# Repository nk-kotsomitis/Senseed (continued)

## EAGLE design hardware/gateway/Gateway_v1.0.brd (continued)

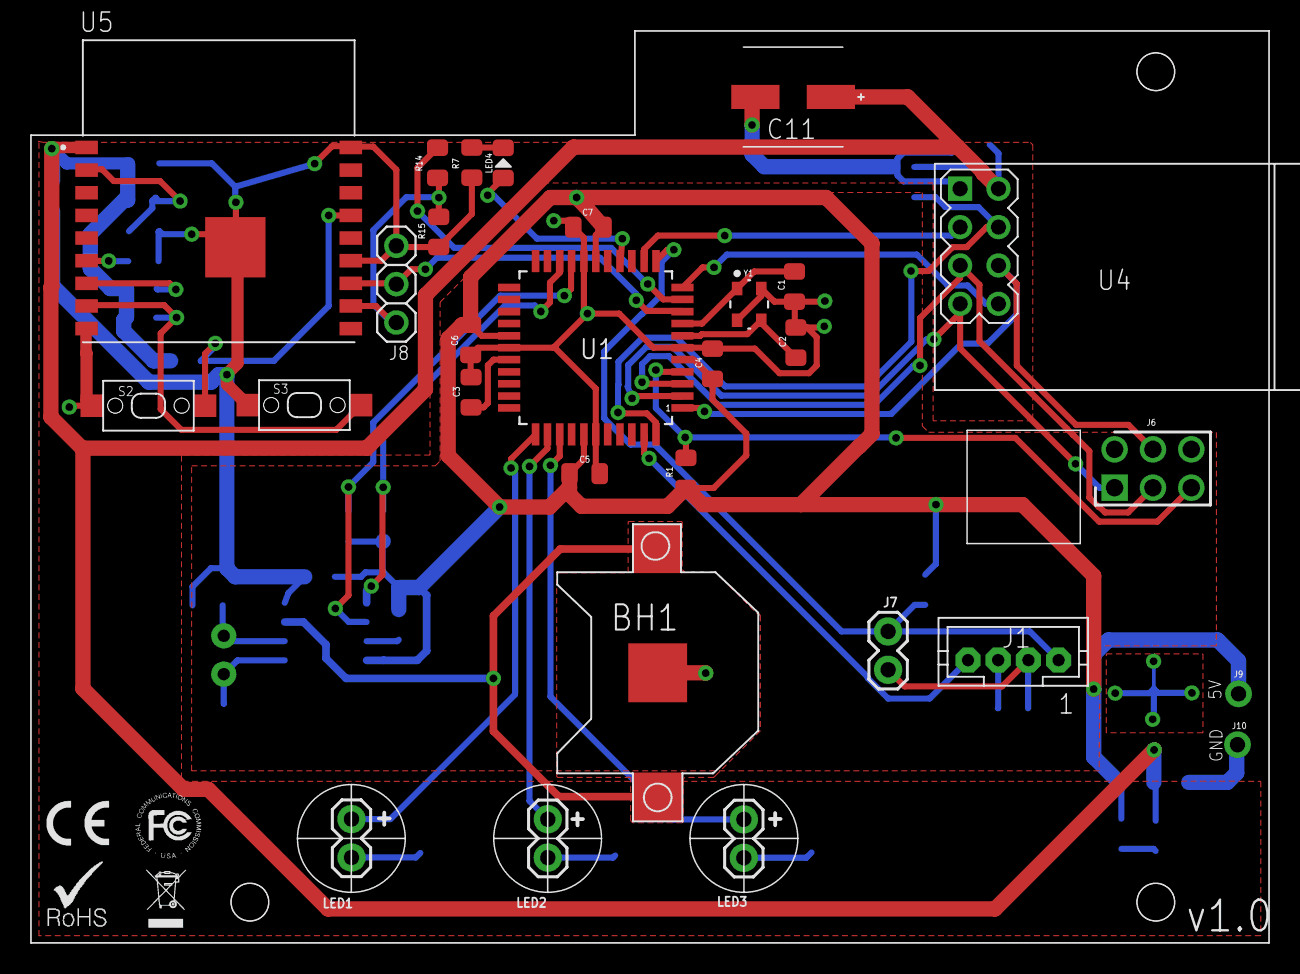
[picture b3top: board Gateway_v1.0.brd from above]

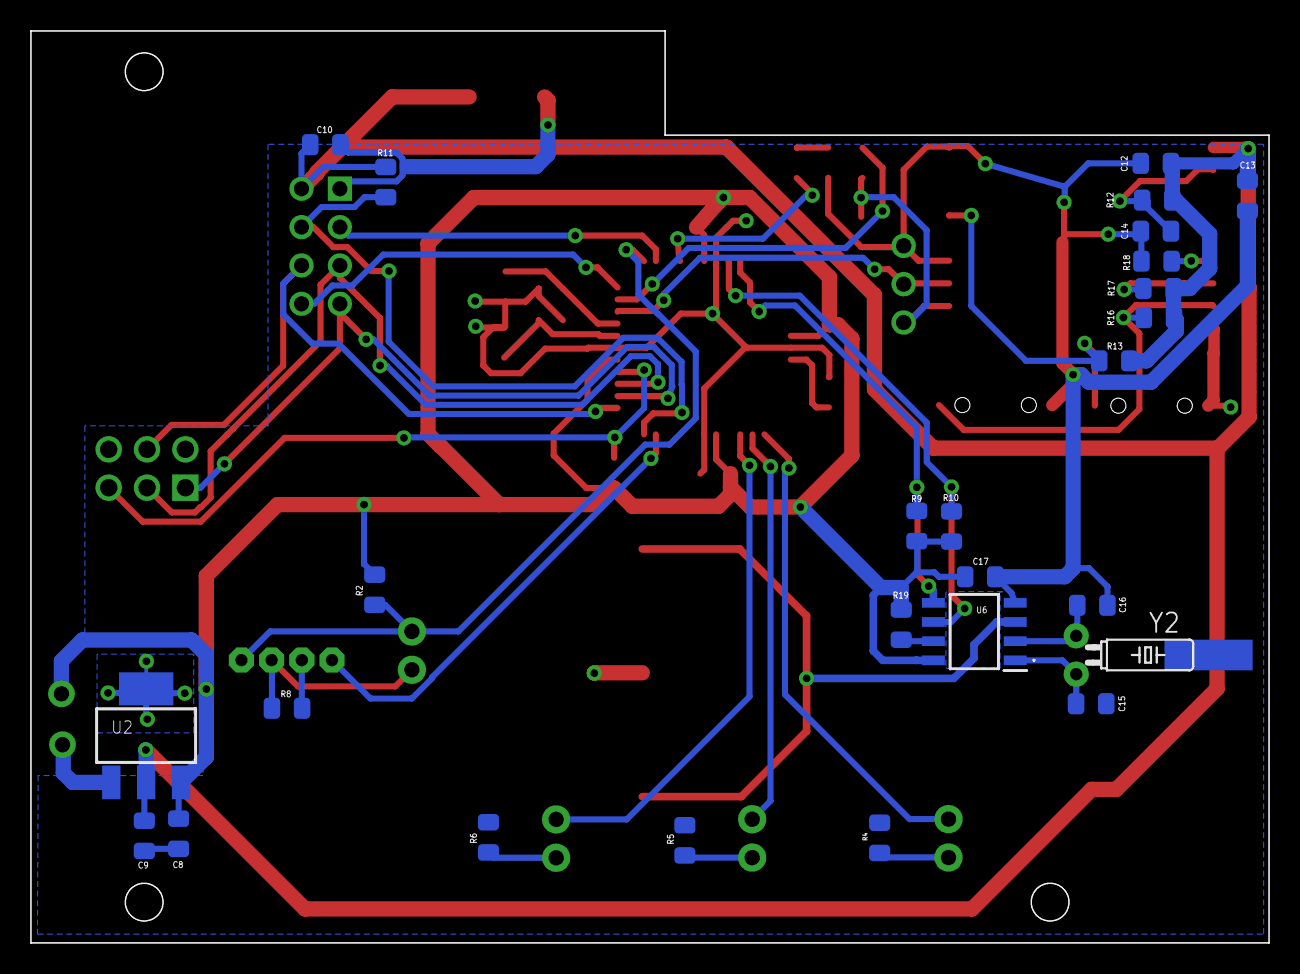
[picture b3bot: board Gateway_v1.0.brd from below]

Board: 2 copper layers, 82.0 x 60.4 mm, 55 parts (26 on the bottom side), 38 nets.

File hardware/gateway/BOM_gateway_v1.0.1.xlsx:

# | Reference Designators | Quantity | MPN | Manufacturer | Part Description | Value | Package | Remark or Link
1 | U1 | 1 | ATMEGA1284-AU | Microchip Technology / Atmel | 8-bit Microcontrollers - MCU AVR 128KB FLSH 4KB EE16KB SRAM-20 MHz | - | TQFP-44
2 | U2 | 1 | SPX1117M3-L-3-3/TR | Maxlinear | LDO Voltage Regulators 3.3V 0.8A Positive | 3.3V 0.8A | SOT-223-3
3 | U4 | 1 | - | - | NRF24L01+ 2.4GHz Wireless RF Transceiver Module | - | Plug In Module - 2x4 2.54mm header | Customer Provided
4 | U5 | 1 | ESP-WROOM-02D(M1102H1600PH3Q0) | Espressif Systems | WiFi Modules (802.11) SMD Module, ESP8266EX, 16Mbits SPI flash, UART Mode, PCB 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 | - | SMD module
5 | U6 | 1 | MCP79410T-I/SN | Microchip Technology | Real Time Clock I2C GP RTCC 1Kb EE 64B SRAM ID | - | SOIC-8
6 | BH1 | 1 | MY-1220-03 | MYOUNG | Coin Cell Battery Holder CR1220 SMT | - | SMD
7 | Y1 | 1 | TXM16M0004322KBCDO00T | TAE(Zhejiang Abel Elec) | ±10ppm 16000000Hz -40℃~85℃ 18pF SMD Passive Crystal Oscillator 35Ω SMD3225-4P C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 | 16 MHz | SMD3225-4P
8 | Y2 | 1 | JFWSH32K25A104C | SHENZHEN JINGFA ELECTRONICS | Radial Cylinder Crystal 32.768KHz ±20ppm 12.5pF 30 KOhm(Max) Radial,3x8mm | 32.768 kHz | OSC-TH Radial 3x8mm
9 | J1 | 1 | PH2.0-4P | CAX | 4-Pin Low-profile PH2.0 Housing Connector | 4 Position | Through Hole
10 | LED1, LED2, LED3 | 3 | 204-10SUGC/S400-A5-L | Everlight Elec | Green 525nm Through Hole 3mm Light Emitting Diodes (LED) - Water Clear | 3mm Green - Clear | Through Hole
11 | LED1, LED2, LED3 | 3 | ERM 1-955 | Bivar | LED Mounting Hardware LED Mount Self Ret Universal LED Black | T-1 3/4 (5mm) | - | Led Spacer
12 | J6 | 1 | C65114 | BOOMELE(Boom Precision Elec) | 2 2.54mm 6 Straight Header，Breakaway P=2.54mm Pin Headers | 6 Position | Through Hole
13 | J7 | 1 | PZ254V-11-02P | XFCN | 2.54mm Straight 2 1 Header，Breakaway Through Hole,P=2.54mm Pin Headers | 2 Position | Through Hole
14 | J8 | 1 | C49257 | BOOMELE(Boom Precision Elec) | 3 2.54mm Straight 1 Header，Breakaway Through Hole Pin Headers | 3 Position | Through Hole
15 | S2, S3 | 2 | TS-1096S-A2B2-C1D2 | Yuandi | SPST Vertical Tactile Switch 3X6X5.0mm SMT | - | SMD
16 | C15, C16 | 2 | 0805CG150J500NT |  | Multilayer Ceramic Capacitor MLCC 15pF ±5% 0805 SMD | 15pF | 0805
17 | C1, C2 | 2 | 0805CG270J500NT |  | Multilayer Ceramic Capacitor MLCC 27pF ±5% 0805 SMD | 27pF | 0805
18 | C3, C4, C5, C6, C7, C13, C14, C17 | 8 | 0805B104M500NT |  | Multilayer Ceramic Capacitor MLCC 100nF ±5% 0805 SMD | 100nF | 0805
19 | C9 | 1 | CL21B225KOFNNNE |  | Multilayer Ceramic Capacitor MLCC 2.2uF X7R ±10% 16V 0805 SMD | 2.2uF | 0805
20 | C8 | 1 | CL21A475KAQNNNE |  | Multilayer Ceramic Capacitor MLCC 4.7uF X5R ±10% 25V 0805 SMD | 4.7uF | 0805
21 | C10, C12 | 2 | GRM21BR61C106KE15L |  | X5R ±10% 16V 10uF 0805 Multilayer Ceramic Capacitors MLCC - SMD/SMT | 10uF | 0805
22 | C11 | 1 | VD1A331ME077000CE0 | Changzhou Huawei Electronics | 6.3mm 330uF 7.7mm 10V 2000hrs 105℃ ±20% -45℃~+105℃ SMD,6.3x7.7mm Aluminum Elect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 | 330uF | 6.3x7.7 SMD
23 | R1, R2, R11, R12, R13, R16, R17, R18 | 8 | 0805W8J1002T5E |  | Chip Resistor - Surface Mount 10K ±5% 1/8W 0805 | 10K | 0805
24 | R14 | 1 | 0805W8J1001T5E |  | Chip Resistor - Surface Mount 1K ±5% 1/8W 0805 | 1K | 0805
25 | R15 | 1 | 0805W8J2001T5E |  | Chip Resistor - Surface Mount 2K ±5% 1/8W 0805 | 2K | 0805
26 | R4, R5, R6, R7, R8, R9, R10, R19 | 8 | 0805W8J0472T5E |  | Chip Resistor - Surface Mount 4.7K ±5% 1/8W 0805 | 4K7 | 0805
 | Off-board components
27 | - | 1 | TC013-N11ASKKUGXX | Well Buying | Tactile Switches TACTILE/JOG SWITCH SPST50mA 12VDC180gf | Illuminated | -
28 | - | 3 | CMC_313_GTP | Visual Communications Company (VCC) | LED Lenses Green Diffused 5mm CMC313GTP | Green | -
29 | - | 1 | - | - | PH2.0 PH 2.0 4pin PH-4p connector with cable 100mm wire 24AWG | PH-4p 100mm 24AWG | -

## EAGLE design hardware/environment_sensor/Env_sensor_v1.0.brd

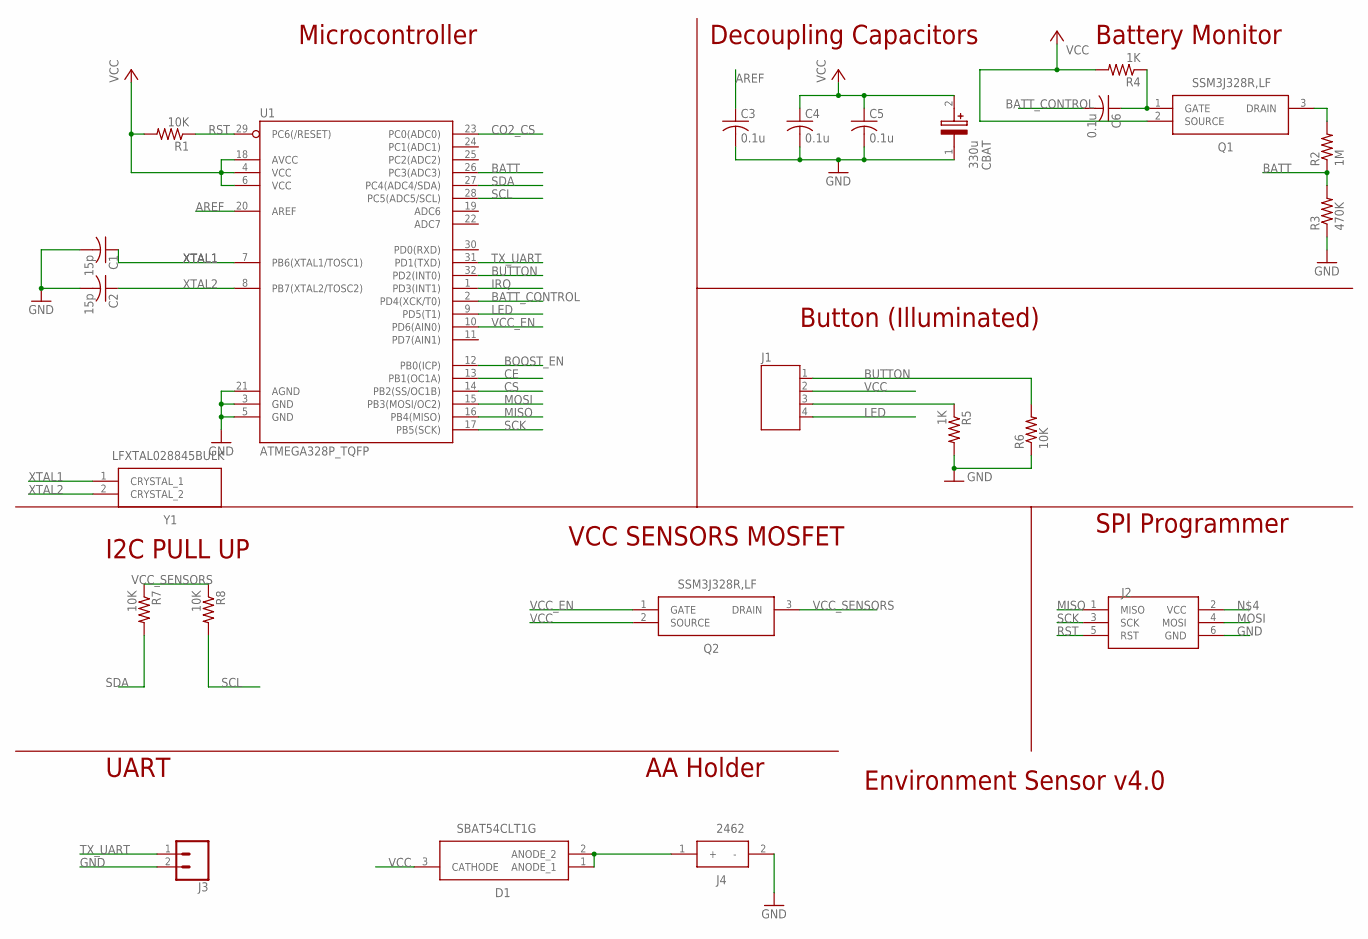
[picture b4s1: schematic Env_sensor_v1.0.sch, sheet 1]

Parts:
C1, C2: 15p; SMD-0805
C3, C4, C5, C6: 0.1u; SMD-0805
CBAT: 330u; SMD_LYTIC_D8
D1: SBAT54CLT1G; SOT96P237X111-3N
J1: JST-PH4
J2: ISP; AVRISP
J3: CONN_02; 1X02
J4: 2462
Q1, Q2: SSM3J328R,LF; SOTFL95P240X88-3N
R1, R6, R7, R8: 10K; SMD-0805
R2: 1M; SMD-0805
R3: 470K; SMD-0805
R4, R5: 1K; SMD-0805
U1: ATMEGA328P_TQFP; TQFP32-08
Y1: LFXTAL028845BULK

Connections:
AREF: C3.1, U1.20 (AREF)
BATT: R2.1, R3.2, U1.26 (PC3(ADC3))
BATT_CONTROL: C6.2, U1.2 (PD4(XCK/T0))
BOOST_EN: U1.12 (PB0(ICP)); also elsewhere on the board
BUTTON: J1.1, R6.2, U1.32 (PD2(INT0))
CE: U1.13 (PB1(OC1A)); also elsewhere on the board
CO2_CS: U1.23 (PC0(ADC0)); also elsewhere on the board
CS: U1.14 (PB2(SS/OC1B)); also elsewhere on the board
GND: C1.2, C2.2, C3.2, C4.2, C5.2, CBAT.1, J2.6 (GND), J3.2, J4.2 (-), R3.1, R5.2, R6.1, U1.3 (GND), U1.5 (GND), U1.21 (AGND); also elsewhere on the board
IRQ: U1.1 (PD3(INT1)); also elsewhere on the board
LED: J1.4, U1.9 (PD5(T1))
MISO: J2.1 (MISO), U1.16 (PB4(MISO)); also elsewhere on the board
MOSI: J2.4 (MOSI), U1.15 (PB3(MOSI/OC2)); also elsewhere on the board
unnamed: Q1.3 (DRAIN), R2.2
unnamed: D1.1 (ANODE_1), D1.2 (ANODE_2), J4.1 (+)
unnamed: J1.3, R5.1
unnamed: C6.1, Q1.1 (GATE), R4.1
RST: J2.5 (RST), R1.1, U1.29 (PC6(/RESET))
SCK: J2.3 (SCK), U1.17 (PB5(SCK)); also elsewhere on the board
SCL: R8.2, U1.28 (PC5(ADC5/SCL)); also elsewhere on the board
SDA: R7.2, U1.27 (PC4(ADC4/SDA)); also elsewhere on the board
TX_UART: J3.1, U1.31 (PD1(TXD))
VCC: C4.1, C5.1, CBAT.2, D1.3 (CATHODE), J1.2, Q1.2 (SOURCE), Q2.2 (SOURCE), R1.2, R4.2, U1.4 (VCC), U1.6 (VCC), U1.18 (AVCC); also elsewhere on the board
VCC_EN: Q2.1 (GATE), U1.10 (PD6(AIN0))
VCC_SENSORS: Q2.3 (DRAIN), R7.1, R8.1; also elsewhere on the board
XTAL1: C1.1, U1.7 (PB6(XTAL1/TOSC1)), Y1.1 (CRYSTAL_1)
XTAL2: C2.1, U1.8 (PB7(XTAL2/TOSC2)), Y1.2 (CRYSTAL_2)

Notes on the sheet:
Environment Sensor v4.0
Decoupling Capacitors
Battery Monitor
SPI Programmer
Microcontroller
UART
AA Holder
Button (Illuminated)
I2C PULL UP
VCC SENSORS MOSFET

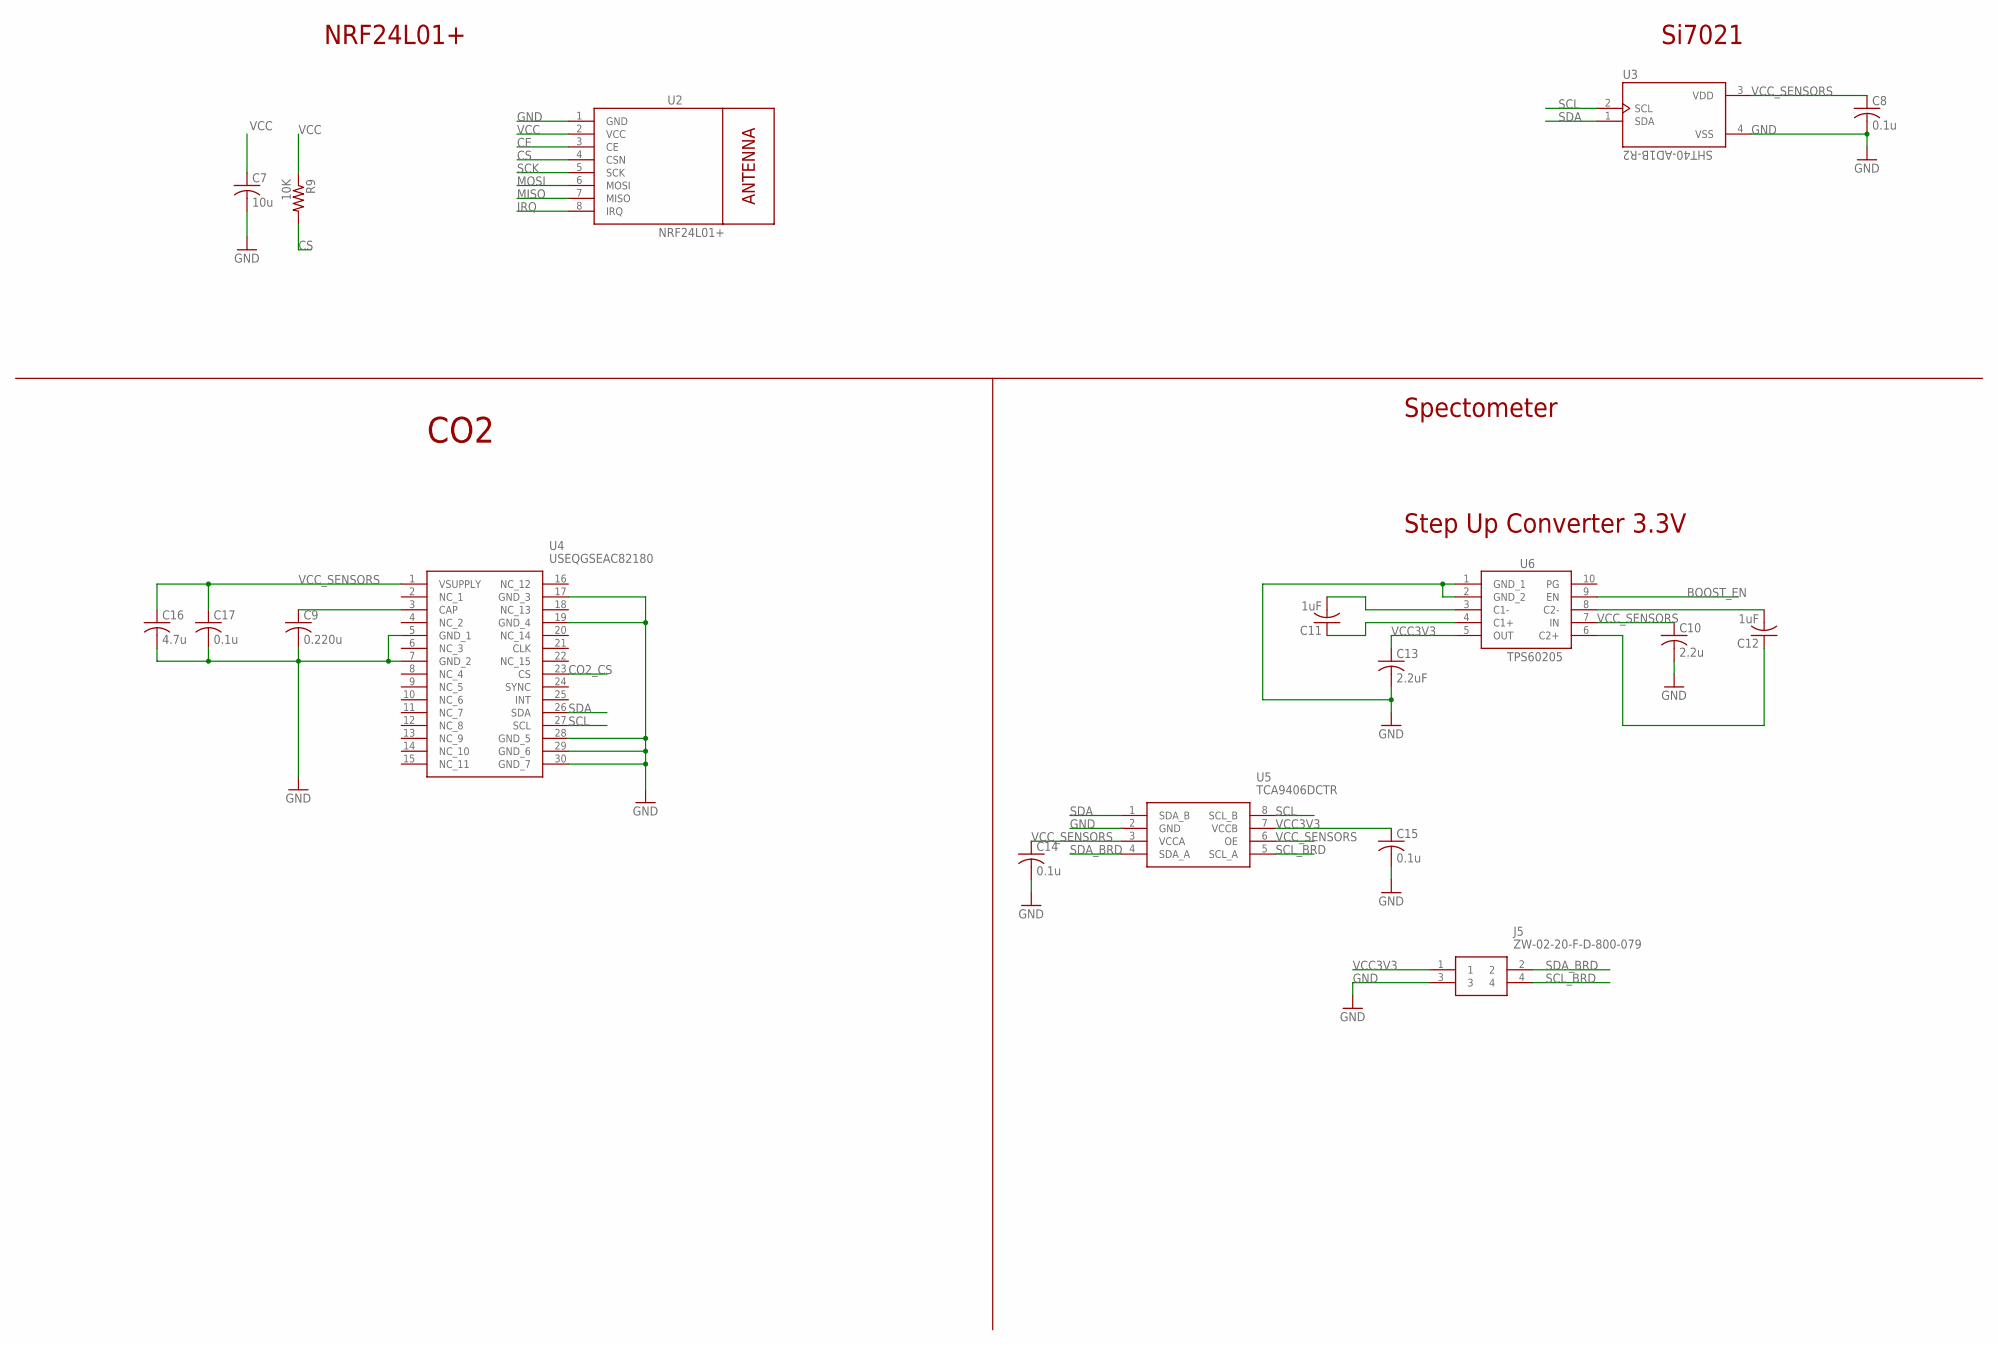
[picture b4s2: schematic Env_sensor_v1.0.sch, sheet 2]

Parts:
C7: 10u; SMD-0805
C8, C14, C15, C17: 0.1u; SMD-0805
C9: 0.220u; SMD-0805
C10: 2.2u; SMD-0805
C11, C12: 1uF; SMD-0805
C13: 2.2uF; SMD-0805
C16: 4.7u; SMD-0805
J5: ZW-02-20-F-D-800-079; HDRV4W64P254_2X2_508X508X2669P
R9: 10K; SMD-0805
U2: NRF24L01+; WIRELESS-NRF24L01
U3: SHT40-AD1B-R2; XDCR_SHT40-AD1B-R2
U4: USEQGSEAC82180
U5: TCA9406DCTR; SOP65P400X130-8N
U6: TPS60205; SOP50P488X107-10N

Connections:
BOOST_EN: U6.9 (EN); also elsewhere on the board
CE: U2.3 (CE); also elsewhere on the board
CO2_CS: U4.23 (CS); also elsewhere on the board
CS: R9.2, U2.4 (CSN); also elsewhere on the board
GND: C7.2, C8.2, C9.2, C10.2, C13.2, C14.2, C15.2, C16.2, C17.2, J5.3, U2.1 (GND), U3.4 (VSS), U4.5 (GND_1), U4.7 (GND_2), U4.17 (GND_3), U4.19 (GND_4), U4.28 (GND_5), U4.29 (GND_6), U4.30 (GND_7), U5.2 (GND), U6.1 (GND_1), U6.2 (GND_2); also elsewhere on the board
IRQ: U2.8 (IRQ); also elsewhere on the board
MISO: U2.7 (MISO); also elsewhere on the board
MOSI: U2.6 (MOSI); also elsewhere on the board
unnamed: C9.1, U4.3 (CAP)
unnamed: C11.1, U6.4 (C1+)
unnamed: C11.2, U6.3 (C1-)
unnamed: C12.1, U6.6 (C2+)
unnamed: C12.2, U6.8 (C2-)
SCK: U2.5 (SCK); also elsewhere on the board
SCL: U3.2 (SCL), U4.27 (SCL), U5.8 (SCL_B); also elsewhere on the board
SCL_BRD: J5.4, U5.5 (SCL_A)
SDA: U3.1 (SDA), U4.26 (SDA), U5.1 (SDA_B); also elsewhere on the board
SDA_BRD: J5.2, U5.4 (SDA_A)
VCC: C7.1, R9.1, U2.2 (VCC); also elsewhere on the board
VCC3V3: C13.1, C15.1, J5.1, U5.7 (VCCB), U6.5 (OUT)
VCC_SENSORS: C8.1, C10.1, C14.1, C16.1, C17.1, U3.3 (VDD), U4.1 (VSUPPLY), U5.3 (VCCA), U5.6 (OE), U6.7 (IN); also elsewhere on the board

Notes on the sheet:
NRF24L01+
Si7021
Spectometer
CO2
Step Up Converter 3.3V

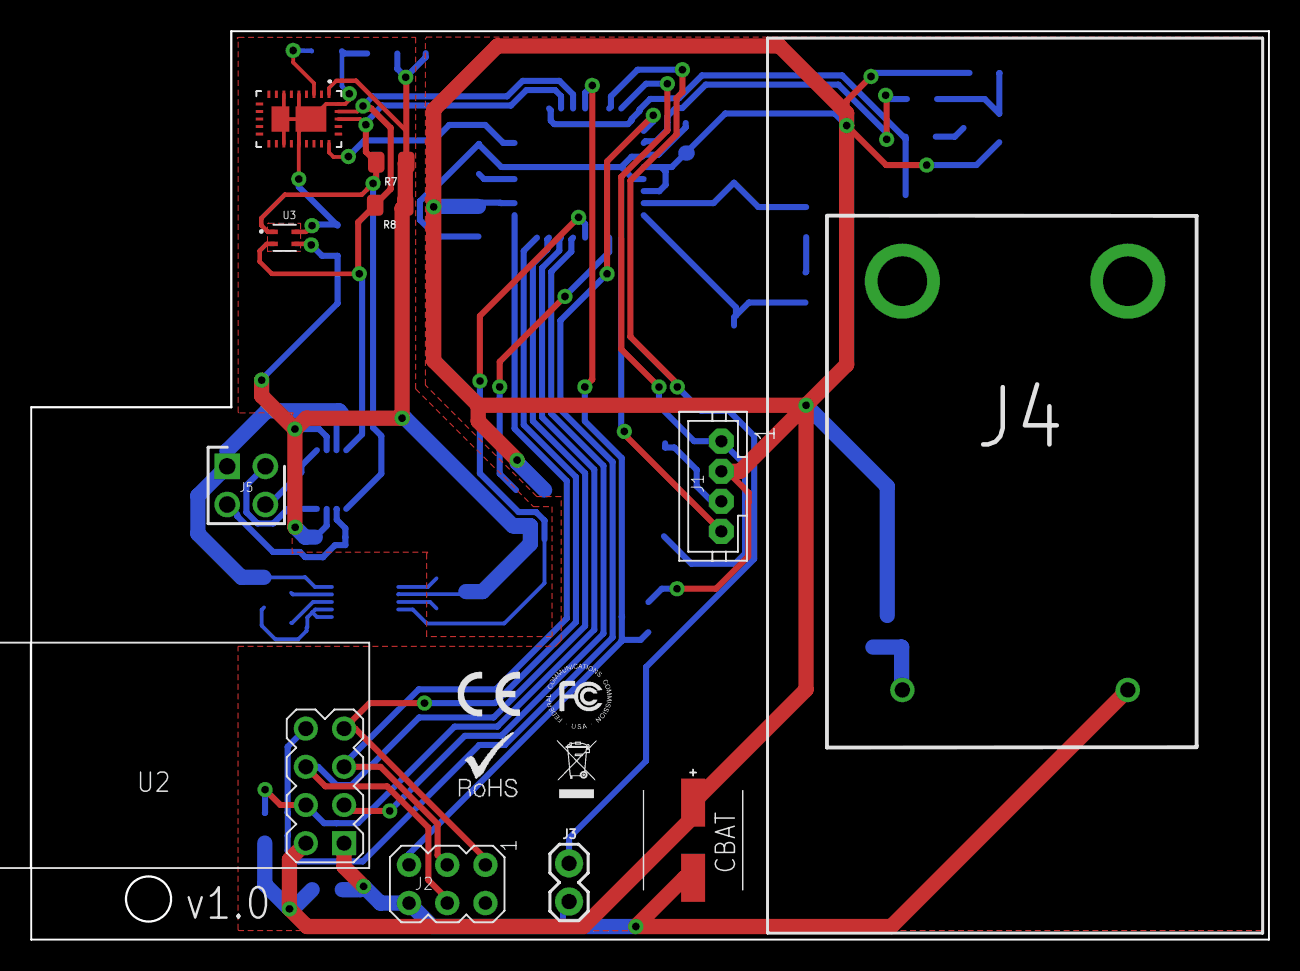
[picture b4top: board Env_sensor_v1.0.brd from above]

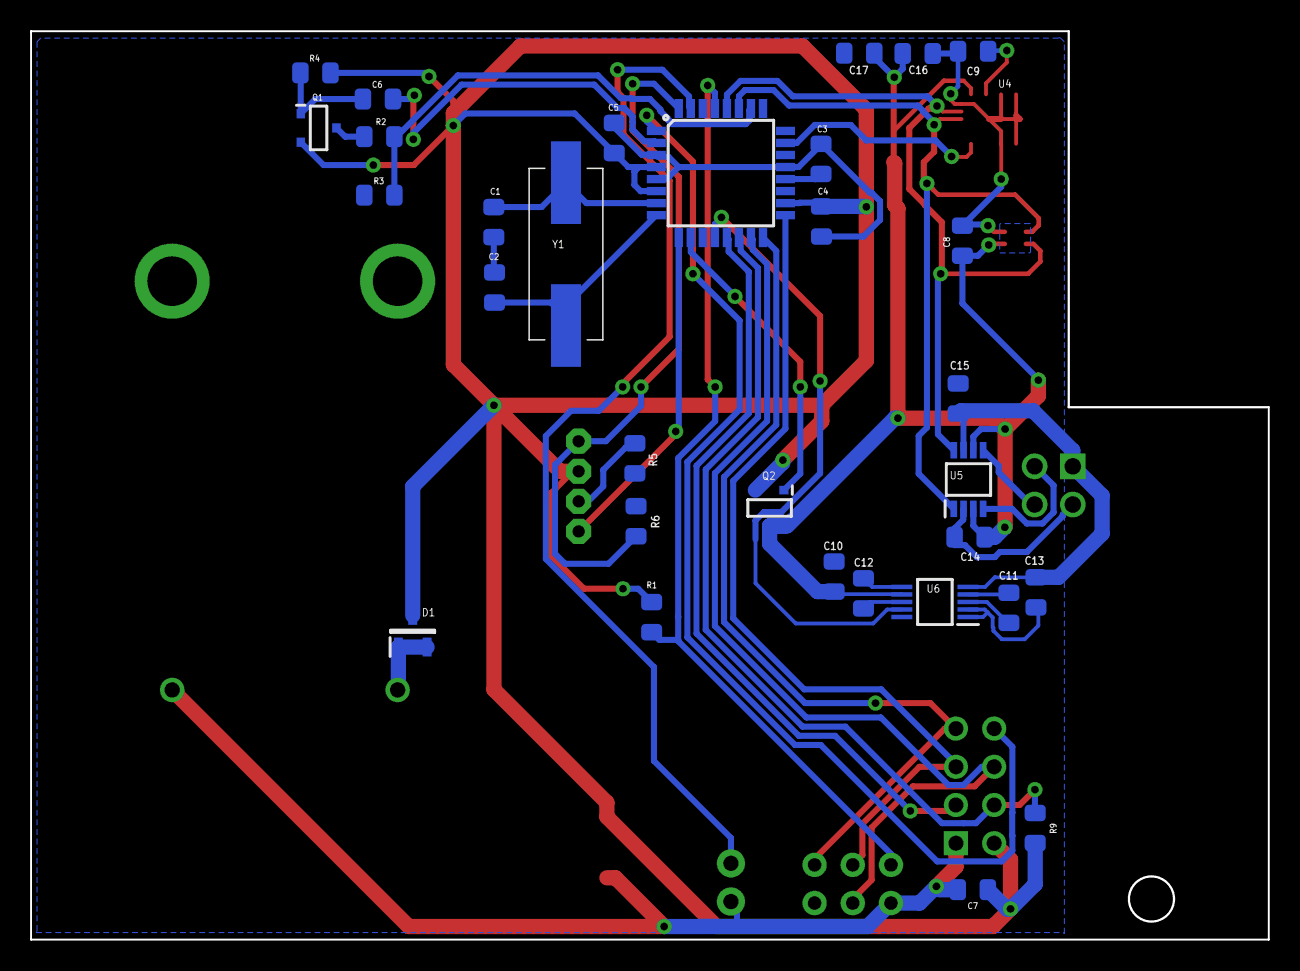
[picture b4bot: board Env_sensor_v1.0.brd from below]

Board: 2 copper layers, 82.3 x 60.4 mm, 42 parts (31 on the bottom side), 35 nets.

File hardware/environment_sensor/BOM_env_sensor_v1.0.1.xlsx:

# | Reference Designators | Quantity | MPN | Manufacturer | Part Description | Value | Package | Remark or Link
1 | U1 | 1 | ATMEGA328P-AU | Microchip Technology / Atmel | 8-bit Microcontrollers - MCU 32KB In-system Flash 20MHz 1.8V-5.5V | - | TQFP-32
2 | U2 | 1 | - | NRF24L01+ 2.4GHz Wireless RF Transceiver Module | - | Plug In Module - 2x4 2.54mm header | Customer Provided
3 | U3 | 1 | SHT40-AD1B-R2 | Sensirion | Board Mount Humidity Sensors RH/ T Sensor | SHT40-AD1B-R2 | DFN-4
4 | U4 | 1 | USEQGSEAC82180 | KEMET | Air Quality Sensors Gas Detector Sensor Digital SMD CO2 | Carbon Dioxide (CO2) | SMD/SMT
5 | U5 | 1 | TCA9406DCTR | Texas Instruments | Translation - Voltage Levels Dual Bidirec 1MHz Vltg Lev-Trans | Translation - Voltage Levels | SM-8
6 | U6 | 1 | TPS60205DGSR | Texas Instruments | Switching Voltage Regulators Regulated 3.3-V Charge Pump | 3.3 V | MSOP-10
7 | Y1 | 1 | TAXM4M2ILFBET2T | TAE(Zhejiang Abel Elec) | ±30ppm -20℃~70℃ 49SMD 20pF 80Ω 4000000Hz HC-49S/SMD Crystals | 4 MHz | HC-49/S
8 | Q1, Q2 | 2 | SSM3J328R,LF | Toshiba | MOSFET P-Ch Sm Sig FET Id -6A -20V -8VGSS | P-channel | SOT-23F-3
9 | D1 | 1 | SBAT54CLT1G | ON Semiconductor | Schottky Diodes & Rectifiers SS DUAL COMMON CATHODE | Si | SOT-23
11 | J1 | 1 | PH2.0-4P | CAX | 4-Pin Low-profile PH2.0 Housing Connector | 4 Position | Through Hole
12 | J2 | 1 | C65114 | BOOMELE(Boom Precision Elec) | 2 2.54mm 6 Straight Header，Breakaway P=2.54mm Pin Headers | 6 Position | Through Hole
13 | J3 | 1 | PZ254V-11-02P | XFCN | 2.54mm Straight 2 1 Header，Breakaway Through Hole,P=2.54mm Pin Headers | 2 Position | Through Hole
14 | J4 | 1 | 2462 | Keystone Electronics | Cylindrical Battery Contacts, Clips, Holders & Springs 2 CELL AA PC HOLDER | AA 2 Battery | Through Hole
15 | J5 | 1 | ZW-02-20-F-D-800-079 | Samtec | Board to Board & Mezzanine Connectors .100" Flex Stack, Flexible Board Stacker,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 | 4 Position | Through Hole
16 | CBAT | 1 | VD1A331ME077000CE0 | Changzhou Huawei Electronics | 6.3mm 330uF 7.7mm 10V 2000hrs 105℃ ±20% -45℃~+105℃ SMD,6.3x7.7mm Aluminum Elect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 | 330uF | 6.3x7.7 SMD
18 | C1, C2 | 2 | 0805CG150J500NT |  | Multilayer Ceramic Capacitor MLCC 15pF ±5% 0805 SMD | 15pF | 0805
19 | C9 | 1 | TCC0805X7R224K500DT |  | 50V 220nF X7R ±10% 0805 Multilayer Ceramic Capacitors MLCC - SMD/SMT | 220nF | 0805
20 | C3, C4, C5, C6, C8, C14, C15, C17 | 8 | 0805B104M500NT |  | Multilayer Ceramic Capacitor MLCC 100nF ±5% 0805 SMD | 100nF | 0805
21 | C11, C12 | 2 | CL21B105KOFNNNE |  | Multilayer Ceramic Capacitor MLCC 1uF X7R ±10% 16V 0805 SMD | 1uF | 0805
22 | C10, C13 | 2 | CL21B225KOFNNNE |  | Multilayer Ceramic Capacitor MLCC 2.2uF X7R ±10% 16V 0805 SMD | 2.2uF | 0805
23 | C7 | 1 | GRM21BR61C106KE15L |  | X5R ±10% 16V 10uF 0805 Multilayer Ceramic Capacitors MLCC - SMD/SMT | 10uF | 0805
24 | C16 | 1 | CL21A475KAQNNNE |  | 25V 4.7uF X5R ±10% 0805 Multilayer Ceramic Capacitors MLCC - SMD/SMT | 4.7uF | 0805
25 | R1, R6, R7, R8, R9 | 5 | RC0805FR-7W10KL |  | Chip Resistor - Surface Mount 10K ±1% 1/4W 0805 | 10K 1/4W | 0805
26 | R2 | 1 | 0805W8J0105T5E |  | Chip Resistor - Surface Mount 1M ±5% 1/8W 0805 | 1M | 0805
27 | R3 | 1 | 0805W8J0474T5E |  | Chip Resistor - Surface Mount 470K ±5% 1/8W 0805 | 470K | 0805
28 | R4, R5 | 2 | 0805W8J1001T5E |  | Chip Resistor - Surface Mount 1K ±5% 1/8W 0805 | 1K | 0805
 | Off-board components
29 | - | 1 | TC013-N11ASKKUGXX | Well Buying | Tactile Switches TACTILE/JOG SWITCH SPST50mA 12VDC180gf | Illuminated | -
30 | - | 1 | - | - | PH2.0 PH 2.0 4pin PH-4p connector with cable 100mm wire 24AWG | PH-4p 100mm 24AWG | -

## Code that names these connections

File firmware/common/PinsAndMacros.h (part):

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#define SPI_SS   DDB4

// CS and CE for NRF24L01
#define RF_CE		DDD4 // PD4
#define RF_CSN		DDB4 // PB4
#define RF_CE_INIT	DDRD |=  (1 << RF_CE);
#define RF_CS_INIT  DDRB |=  (1 << RF_CSN);
#define RF_CE_HIGH  PORTD |=  (1 << RF_CE);
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#define TIMER_2_TICK_MS		0.064

// Modules/Leds/Buttons
#define CONSUMPTION	0x04	// PA2
#define RELAY1		0x08	// PA3
#define NRF_CONTROL	0x20	// PD5
#define ESP_CONTROL	0x10	// PA4
#define BUTTON_1	0x04	// PB2
#define BUTTON_3	0x02	// PA1
#define LED1 0x02			// PB1
#define LED2 0x01			// PB0
#define LED3 0x01			// PA0
#define LED4 0x40 			// PD6
#define LED5 0x08			// PB3

#define consumption_init	DDRA&=~CONSUMPTION
#define relay_1_init	DDRA|=RELAY1
#define relay_1_on		PORTA|=RELAY1
#define relay_1_off		PORTA&=~RELAY1
#define relay_1_toggle	PORTA^=RELAY1
#define relay_1_read	((PORTA&RELAY1)>>3)

#define button_1_init	DDRB&=~BUTTON_1
#define button_1_pushed !(PINB&BUTTON_1)
#define button_1_pushed_seconds 3

#define led_1_init		DDRB|=LED1		// Internet
#define led_1_on		PORTB|=LED1
#define led_1_off		PORTB&=~LED1
#define led_1_toggle	PORTB^=LED1

#define led_2_init		DDRB|=LED2		// WPS
#define led_2_on		PORTB|=LED2
#define led_2_off		PORTB&=~LED2
#define led_2_toggle	PORTB^=LED2

#define led_3_init		DDRA|=LED3		// Warning
#define led_3_on		PORTA|=LED3
#define led_3_off		PORTA&=~LED3
#define led_3_toggle	PORTA^=LED3

#define led_4_init		DDRD|=LED4		// NRF packets
#define led_4_on		PORTD|=LED4
#define led_4_off		PORTD&=~LED4
#define led_4_toggle	PORTD^=LED4

#define led_5_init		DDRB|=LED5		// Relay status
#define led_5_on		PORTB|=LED5
#define led_5_off		PORTB&=~LED5
#define led_5_toggle	PORTB^=LED5


#define INTERNET_LED_ON			{TIMSK0&=(0 << OCIE0A); led_1_on;}
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

#define interrupt_0_init	{ EICRA |= _BV(ISC01); EIMSK |= _BV(INT0); }	// IRQ
#define interrupt_1_init	{ EICRA |= _BV(ISC11); EIMSK |= _BV(INT1); }	// Button2 - TX_debug
#define interrupt_2_init	{ EICRA |= _BV(ISC21); EIMSK |= _BV(INT2); }	// Button1

//interrupt_1_init; // Disabled because we need TX debug TODO

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#define SOIL_CAP_4 GETBIT(PORTC3)
#define SOIL_CAP_4_ADC_CH PORTC3
#define SOIL_CAP_4_INIT {DDRC&=~SOIL_CAP_4; PORTC&=~SOIL_CAP_4;}
// Unused Pins: PC5, ADC6, ADC7, PD0, PD1 (Tx Debug). Set to inputs with pull-up
// TODO: PORTC7 and PD1 (Tx Debug)
#define UNUSED_PINS_C (GETBIT(PORTC5) | GETBIT(PORTC6)) // | GETBIT(PORTC7));
#define UNUSED_PINS_C_INIT { {DDRC &= ~(UNUSED_PINS_C); PORTC |= UNUSED_PINS_C;} }
#define UNUSED_PINS_D (GETBIT(PORTD1))
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#define VCC_EN_ON PORTD|=VCC_EN
#define VCC_EN_OFF PORTD&=~VCC_EN
// Boost Enable
#define BOOST_EN GETBIT(PORTB0)
#define BOOST_EN_INIT {DDRB|=BOOST_EN; BOOST_EN_OFF;} // Initialize and set to low BOOST_EN_OFF
#define BOOST_EN_ON PORTB|=BOOST_EN
#define BOOST_EN_OFF PORTB&=~BOOST_EN
// Battery Control
#define BATT_CTRL GETBIT(PORTD4)
#define BATT_CTRL_INIT {DDRD|=BATT_CTRL; BATT_CTRL_OFF;} // Initialize and set to low BATT_CTRL_OFF
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#define BATTERY_ADC_CH PORTC3
#define BATTERY_INIT {DDRC&=~BATTERY; PORTC&=~BATTERY;}
// CO2 - Digital Output
#define CO2_CS GETBIT(PORTC0)
#define CO2_CS_INIT DDRC|=CO2_CS
#define CO2_CS_ON PORTC|=CO2_CS
#define CO2_CS_OFF PORTC&=~CO2_CS
	
// Unused Pins: PC1, PC2, ADC6, ADC7, PD0, PD1 (Tx Debug), PD7. Set to inputs with pull-up
// TODO: PORTC7 and PD1 (Tx Debug)
#define UNUSED_PINS_C (GETBIT(PORTC1) | GETBIT(PORTC2) | GETBIT(PORTC6)) // | GETBIT(PORTC7));
#define UNUSED_PINS_C_INIT { {DDRC &= ~(UNUSED_PINS_C); PORTC |= UNUSED_PINS_C;} }
#define UNUSED_PINS_D (GETBIT(PORTD0) | GETBIT(PORTD7)) // | GETBIT(PORTD7)
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
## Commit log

2025-03-04 Removed word
2025-05-25 Create LICENSE
